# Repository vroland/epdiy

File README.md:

EPDiy E-Paper Driver
=======================================

EPDiy is a driver board which talks to affordable E-Paper (or E-Ink) screens, which are usually sold as replacement screens for E-Book readers. Why are they interesting?

* Easy on the eyes and paper-like aesthetics
* No power consumption when not updating
* Sunlight-readable

Ready-made DIY modules for this size and with 4bpp (16 Grayscale) color support are currently quite expensive and / or slow.
The EPDiy controller can drive the bare display modules, e.g. from old e-Readers, which are available for 20$ (small) / 30$ (large) on ebay!
Additionally, since it is based on the ESP32S3 (V7) / ESP32 (V2-V6) microcontroller, it features WiFi and Bluetooth connectivity.

The EPDiy driver board targets a range of E-Paper displays, as shown in the table below.
As the driving method for all matrix-based E-ink displays is more or less the same, only the right connector and timings are needed.
The current V7 board has three different display connectors, other display will require an adapter board.

The controller is optimized for the use with LiPo batteries, featuring a LiPo charger and ultra-low deep sleep current.

This project supports a driver for the ESP-IDF and Arduino. For installation instructions, please refer to the [documentation](https://epdiy.readthedocs.io/en/latest/getting_started.html#getting-your-board).
Note that for epdiy V7, update speeds are significantly lower when using the Arduino IDE, because it does not allow to change
the sub-optimal cache configuration.

Get Inspired
------------

The `examples` directory contains some example applications like a weather station or a screen diagnostic test. 
If you want to build something more useful though, how about:

- A serial terminal for connecting to a raspberry pi: [video](https://cdn.hackaday.io/files/1681937195969312/terminal_demo.mp4) [repository](https://github.com/vroland/epdiy-terminal)]
- A Music Player Daemon (MPD) dashboard: [repository](https://github.com/vroland/epdiy-mpd)]
- Firmware for displaying images directly from Immich (Self-Hosted Photo Management) [epdiy-immich](https://github.com/vroland/epdiy-immich)
- An e-Paper picture frame: [video](https://www.youtube.com/watch?v=r7AcNQsSZUw)
- And more to come!

Building It
-----------

On the [EPDiy Hardware Page](https://vroland.github.io/epdiy-hardware/), you'll find a list of all boards and variants, adapters, and helpers.
Next to each board, there are manufacturing files (gerbers), Bill of Materials (BoM), part placement files,
and 3D models ready to use!

For ordering from JLCPCB for example, ordering is as easy as downloading the zipped gerbers, BoM, and placement file
and uploading them. The process is very similar for other manufacturers, check your vendor's documentation for details.
Don't forget to oder adapters if the board doesn't have connectors for your specific display.

The current latest version is epdiy V7, beased on the ESP32S3. 
Older versions are also available on the hardware page.

#### Contributing Hardware

Want to contribute your own board variant or adapter? 
Check out the [epdiy-hardware repository](https://github.com/vroland/epdiy-hardware) for instructions.

Gettings Started
----------------

For instructions and more information visit the [documentation](https://epdiy.readthedocs.io/en/latest/getting_started.html)!

Join the Discussion
----------------

 -  Matrix Community: +epdiy:matrix.vroland.de
 - Slack: See badge

Displays
--------

|Name      |Size |Resolution|Compatible|Connector|Pin count|Compatible since pcb version|Notes
| --:      | --: | --:       | --:         | --:                  | --: | --: | --: |
| ED060SC4 | 6"  | 800 x 600<br>167 PPI | yes, tested | FH26W-39S-0.3SHW(60) | 39  | v2  |     |
|ED097OC4|9.7"|1200 x 825<br>150 PPI|yes, tested|XF2M-3315-1A|33|v2|Cheap, inferior contrast
|ED097TC2|9.7"|1200 x 825<br>150 PPI|yes, tested|XF2M-3315-1A|33|v2|Slightly higher price, better contrast
|ED097OC1|9.7"|1200 x 825<br>150 PPI|yes (should work)|XF2M-3315-1A|33|v2|Cheap, inferior performance
|ED047TC1|4.7"|960 x 540<br>234 PPI|yes, tested|40-pin|40|LILYGO 4.7" EPD|Supported only by 4.7" e-paper board by LILYGO
| ED050SC5 | 5" | 600 x 800<br>200 PPI | yes, tested       | THD0510-33CL-GF | 33 | v5 |
| ED050SC3 | 5" | 600 x 800<br>200 PPI | yes (should work) | THD0510-33CL-GF | 33 | v5 |
| ED052TC4 | 5.2" | 1280 x 780<br>??? PPI | yes (should work) | WP27D-P050VA3 | 50 | v5 |
| ED133UT2 | 13.3" | 1600 x 1200<br>150 PPI | yes, tested | adapter board | 39 | v2 | Adapter Board required, also PENG133D
| ED060XC3 | 6" | 758 x 1024<br>212 PPI | yes, tested | THD0515-34CL-SN | 34 | v5 | Cheapest, good contrast and resolution
| ED060XD4 | 6"  | 758 x 1024<br>212 PPI | yes, tested | THD0515-34CL-SN | 34 | v5 |
| ED060XC5 | 6"  | 758 x 1024<br>212 PPI | yes (should work as ED060XC3) | THD0515-34CL-SN | 34 | v5 |
| ED060XD6 | 6"  | 758 x 1024<br>212 PPI | yes (should work as ED060XC3) | THD0515-34CL-SN | 34 | v5 |
| ED060XH2 | 6"  | 758 x 1024<br>212 PPI | yes (should work as ED060XC3) | THD0515-34CL-SN | 34 | v5 |
| ED060XC9 | 6"  | 758 x 1024<br>212 PPI | yes (should work as ED060XC3) | THD0515-34CL-SN | 34 | v5 |
| ED060KD1 | 6"  | 1072 x 1448<br>300 PPI | yes (should work as ED060XC3) | THD0515-34CL-SN | 34 | v5 |
| ED060KC1 | 6"  | 1072 x 1448<br>300 PPI | yes (should work as ED060XC3) | THD0515-34CL-SN | 34 | v5 |
| ED060SCF | 6" | 600 x 800<br>167 PPI | yes, tested | THD0515-34CL-SN | 34 | v5 | Different flex cable shape
| ED060SCN | 6" | 600 x 800<br>167 PPI | yes (should work as ED060XC3) | THD0515-34CL-SN | 34 | v5 | Different flex cable shape
| ED060SCP | 6" | 600 x 800<br>167 PPI | yes (should work as ED060XC3) | THD0515-34CL-SN | 34 | v5 | Different flex cable shape
| ED060SC7 | 6" | 600 x 800<br>167 PPI | yes (should work) | AXT334124 | 34 | v5 | connector dropped in v6
| ED060SCG | 6"  | 600 x 800<br>167 PPI | yes (should work) | AXT334124 | 34 | v5 | connector dropped in v6
| ED060SCE | 6"  | 600 x 800<br>167 PPI | yes (should work) | AXT334124 | 34 | v5 | connector dropped in v6
| ED060SCM | 6"  | 600 x 800<br>167 PPI | yes (should work) | AXT334124 | 34 | v5 | connector dropped in v6
| ED060SCT | 6"  | 600 x 800<br>167 PPI | yes, tested       | AXT334124 | 34 | v5 | connector dropped in v6
| ED078KC1 | 7.8"  | 1872 x 1404<br>300 PPI | yes, tested     | FH12-40S-0.5SH | 40 | v7 | 16 data lines

Troubleshooting
---------------

The following list is compiled from past experiences and GitHub issues:
 * **The displayed image displays only part of the image.** Make sure to select the correct display type as described [here](https://epdiy.readthedocs.io/en/latest/getting_started.html#selecting-a-display-type).
 * **The existing image fades / darkens when updating a partial screen region.** Make sure the VCOM voltage is [calibrated](https://epdiy.readthedocs.io/en/latest/getting_started.html#calibrate-vcom) for your specific display.
 * **The second third of the image is replaced with the last third.** This seems to be a timing issue we could not yet quite figure out the reason for. For a workarround or suggestions please [join the discussion](https://github.com/vroland/epdiy/issues/15).
 * **The ESP does not boot correctly when external periperals are connected.** Make sure not to pull GPIO12 high during boot, as it is a strapping pin internal voltage selection (https://github.com/vroland/epdiy/issues/17).
 * **The ESP power consumption in deep sleep is too high.** Add `rtc_gpio_isolate(GPIO_NUM_12);` to your solution. See also [Configuring IOs (Deep-sleep Only)](https://docs.espressif.com/projects/esp-idf/en/latest/esp32/api-reference/system/sleep_modes.html?highlight=rtc_gpio_isolate#configuring-ios-deep-sleep-only).

LilyGo Boards
---------------

### Supported LilyGo Boards

| Board | Display | Board Definition | Notes |
| --: | --: | --: | --: |
| LilyGo T5 4.7" | ED047TC1 | `epd_board_lilygo_t5_47` | Original T5 4.7" |
| LilyGo T5 S3 E-Paper Pro | ED047TC1 | `epd_board_v7` | ESP32-S3 based, includes GT911 touch, PCF8563 RTC, BQ25896/BQ27220 battery management |

### Power Management

There are several differences with these boards.
One particular one is the way the LilyGo handles power to the display the official lilygo code has two states.
This is now handled in epdiy in a different way to the lilygo code.
**epd_poweroff()** completely turns the power off to the display and the other peripherals of the lilygo.
The new function **epd_powerdown()** keeps the peripherals on (this allows the touch functions to continue to work).
**epd_poweroff() should always be called before sleeping the system**
You can still use touch to wake the screen with the following.
In Arduino it works like this.
`epd_poweroff();`

 `epd_deinit();`

 `esp_sleep_enable_ext1_wakeup(GPIO_SEL_13, ESP_EXT1_WAKEUP_ANY_HIGH);`

 `esp_deep_sleep_start();`

### I2C Bus Sharing

EPDIY now uses the ESP-IDF master bus/device I2C driver on IDF 5.x and newer.

Existing programs can keep calling `epd_init(...)` and EPDIY will create and own the board's default I2C bus.

If your application already owns an ESP-IDF I2C master bus, pass it in during initialization:

```c
i2c_master_bus_handle_t bus = ...;
EpdI2cConfig i2c_config = {
    .bus_handle = bus,
};
EpdInitConfig init_config = {
    .i2c = &i2c_config,
};

epd_init_with_config(&epd_board_v7, &ED047TC1, EPD_LUT_64K, &init_config);
```

When a bus handle is provided, EPDIY will attach its TPS65185/PCA9555 devices to that bus and leave bus ownership to the caller.

More on E-Paper Displays
------------------------

 * List of E-Paper devices and their screens: https://e-ink-reader.ru/chg_dsp_en.php (thanks, @mcer12)
 * Reverse engineering of display pins, possible starting point for alternative drivers: https://linux-sunxi.org/PocketBook_Touch_Lux_3 (thanks, @mcer12)
 * Reverse engineering and explanation on driving EPDs: http://essentialscrap.com/eink/index.html
 * Earlier take on driving 6" EPDs with an ESP32, basis of original power circuit: http://spritesmods.com/?art=einkdisplay&page=1
 * Related Hackaday projects: https://hackaday.io/project/21607 https://hackaday.io/project/11537

If you know any other useful resources or have suggestions, please comment on #31!

Hackaday Project
----------------

For more details, see the project page on Hackaday: https://hackaday.io/project/168193-epdiy-976-e-paper-controller

Licenses
--------

The weather example is Copyright (c) David Bird 2018 (except for minor modifications). Please refer to `examples/weather/README.md` for details.

The board and schematic are licensed under a  <a rel="license" href="https://creativecommons.org/licenses/by-sa/4.0/">Creative Commons Attribution-ShareAlike 4.0 International License</a>.

Firmware and remaining examples are licensed under the terms of the GNU Lesser GPL version 3.
Utilities are licensed under the terms of the MIT license.

### Checked V7 power transitions

Applications that need to recover from a display supply failure can use
`epd_poweron_checked()` and `epd_poweroff_checked()` on board V7. Draw only after
power-on returns `ESP_OK`, and check shutdown too. Other boards return
`ESP_ERR_NOT_SUPPORTED` without changing power; the existing void power API is
still available for legacy callers.

V7 waits up to 500 ms **per power-good phase**, using the monotonic microsecond
clock. Polls yield for 10 ms (at least one FreeRTOS tick). PCA9555 and TPS65185
transfers have a 50 ms timeout, including writes and cleanup. A phase can overrun
its deadline by one bounded transfer or poll; setup and shutdown take additional
time. These constants live in `src/board/power_timing.h`.

On a failed start, V7 attempts both shutdown writes and returns the original
error. A cleanup failure is logged separately: if I2C is broken, software cannot
guarantee physical rail shutdown. The checked VCOM preparation callback follows
the same rules. Legacy void callers cannot inspect the returned status and
should migrate before relying on automatic recovery.

Run `python3 test/host/test_power.py` for host fault tests at two tick rates.

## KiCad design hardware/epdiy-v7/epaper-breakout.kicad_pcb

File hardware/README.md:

KiCad project of the breakout board.

<br />This work is licensed under a <a rel="license" href="http://creativecommons.org/licenses/by/4.0/">Creative Commons Attribution 4.0 International License</a>.

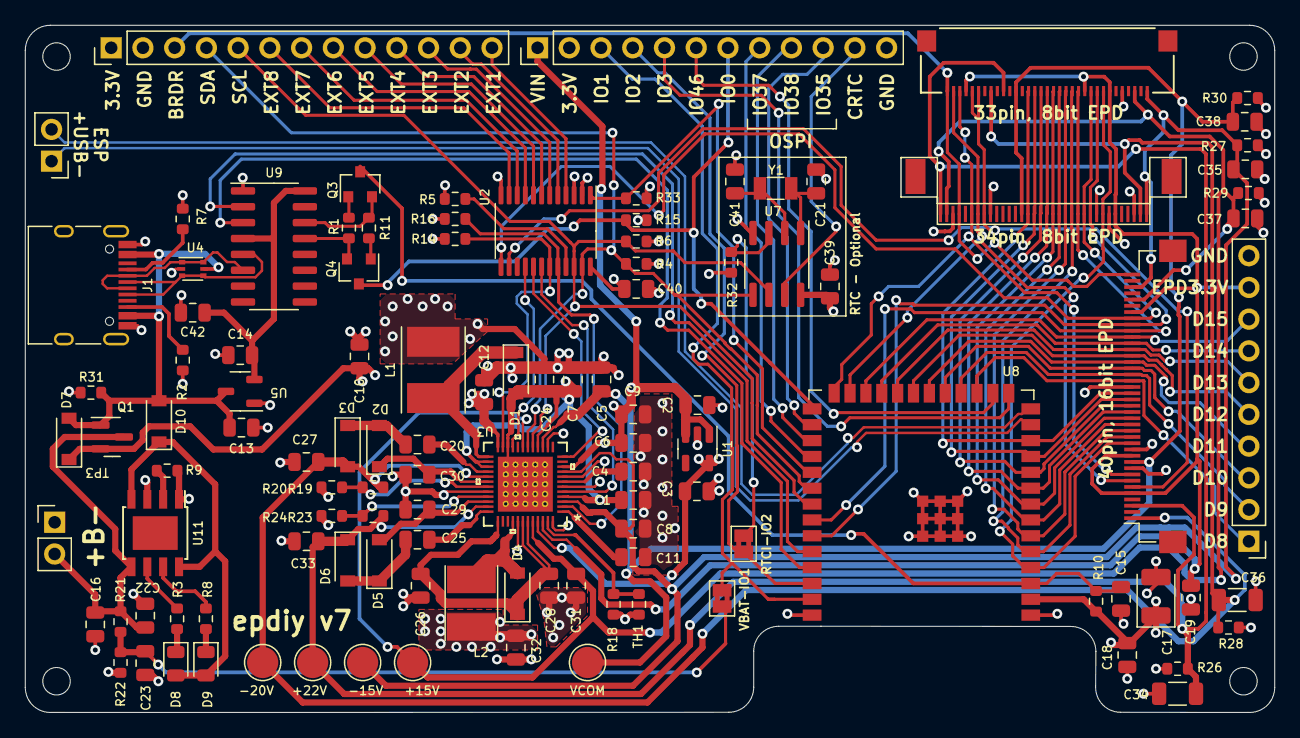
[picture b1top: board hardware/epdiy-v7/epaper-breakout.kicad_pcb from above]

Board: 4 copper layers, 100.0 x 55.0 mm, 117 parts (0 on the bottom side), 100 nets.

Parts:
C1, C4, C5, C7, C8, C11, C24, C26, C28, C31: 4.7uF; C_0805_2012Metric
C2, C3, C9, C12, C16, C19, C32: 10uF; C_0805_2012Metric
C6, C10: 22uF; C_0805_2012Metric
C13, C14, C18: 1uF; C_0805_2012Metric
C15, C22, C23, C29, C30, C39, C40, C42: 100nF; C_0805_2012Metric
C17: 100uF; CP_EIA-3528-15_AVX-H
C20, C25: 10nF; C_0805_2012Metric
C21, C41: 12pF; C_0805_2012Metric
C27, C33: 2.2uF; C_0805_2012Metric
C34, C36: 1uF/50V; C_1206_3216Metric
C35, C37, C38: 1uF/25V; C_0805_2012Metric
D1, D2, D3, D4, D5, D6, D7: MBR0540; D_SOD-123
D8: LED GREEN; LED_0805_2012Metric
D9: LED RED; LED_0805_2012Metric
D10: 1N5817; D_SOD-123
H1, H2, H3, H4: MountingHole; MountingHole_2.2mm_M2
J1: USB_C_Receptacle_USB2.0; USB_C_Receptacle_HRO_TYPE-C-31-M-12
J2: EXTENSION_HEADER; PinHeader_1x13_P2.54mm_Vertical
J3: USB_HDR; PinHeader_1x02_P2.54mm_Vertical
J4: XF2M-3315-1A; CONN_ED097OC4
J5: CONN_BAT; PinHeader_1x02_P2.54mm_Vertical
J6: 8BIT_HEADER; PinHeader_1x10_P2.54mm_Vertical
J7: ESP_HDR; PinHeader_1x12_P2.54mm_Vertical
JP1: VBAT_GPIO2; SolderJumper-2_P1.3mm_Bridged2Bar_Pad1.0x1.5mm
JP2: RTCINT_GPIO1; SolderJumper-2_P1.3mm_Bridged2Bar_Pad1.0x1.5mm
L1: 4.7uH; L_Taiyo-Yuden_NR-50xx_HandSoldering
L2: 2.2uH; L_Taiyo-Yuden_NR-40xx_HandSoldering
Q1: AO3401A; SOT-23
Q3, Q4: MMBT3904; SOT-23
R1, R4, R6, R10, R11, R14, R15, R16, R32, R33: 10k; R_0603_1608Metric
R2, R7: 5.1k; R_0603_1608Metric
R3, R8: 1k; R_0603_1608Metric
R5: 0; R_0603_1608Metric
R9: 6.8k; R_0603_1608Metric
R18: 43k; R_0603_1608Metric
R19, R23: 1M; R_0603_1608Metric
R20: 52.3k; R_0603_1608Metric
R21: 680k; R_0603_1608Metric
R22: 150k; R_0603_1608Metric
R24: 47.5k; R_0603_1608Metric
R26, R27, R28, R29: 47k; R_0603_1608Metric
R30, R31: 100k; R_0603_1608Metric
TH1: 10k/3380K; R_0603_1608Metric
TP1: +22V; TestPoint_Pad_D2.5mm
TP2: -15V; TestPoint_Pad_D2.5mm
TP3: -20V; TestPoint_Pad_D2.5mm
TP4: +15V; TestPoint_Pad_D2.5mm
TP5: VCOM; TestPoint_Pad_D2.5mm
U1: RT9080-33GJ5; TSOT-23-5
U2: PCA9535PW; TSSOP-24_4.4x7.8mm_P0.65mm
U3: TPS651851RSLR
U4: USBLC6-2P6; SOT-666
U5: XC6206PxxxMR; SOT-23-3
U6: ED078KH6; Hirose_FH12-40S-0.5SH_1x40-1MP_P0.50mm_Horizontal
U7: PCF8563T; SOIC-8_3.9x4.9mm_P1.27mm
U8: ESP32-S3-WROOM-1
U9: CH340C; SOIC-16_3.9x9.9mm_P1.27mm
U10: ED060XC5; X05A20H34G
U11: TP4056; TP4056_SOP-8-PP
Y1: 32.768K; Crystal_SMD_3215-2Pin_3.2x1.5mm

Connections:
3.3V: C3.2, C17.1, C18.2, C39.2, C40.1, J2.1, J7.2, R4.1, R6.1, R10.2, R14.1, R15.2, R16.1, R32.2, R33.1, U1.5 (VOUT), U2.24 (VDD), U3.45 (VIN3P3), U7.8 (VDD), U8.2 (3V3)
/15V: C31.2, C37.1, J4.3 (VPOS), R29.1, TP4.1, U3.19 (VPOS_DIS), U3.44 (VPOS), U6.36 (VPOS), U10.33 (VPOS)
/+22V: C33.1, C34.1, D6.1 (K), J4.24 (VGG), R23.1, R26.1, TP1.1, U3.35 (VDDH_DIS), U6.3 (VGH), U10.34 (VGG)
/-15V: C8.2, C35.1, J4.1 (VNEG), R27.1, TP2.1, U3.3 (VNEG), U3.9 (VNEG_DIS), U6.38 (VNEG), U10.1 (VNEG)
/-20V: C27.2, C36.1, D3.2 (A), J4.26 (VEE), R19.1, R28.1, TP3.1, U3.29 (VEE_DIS), U6.1 (VGL), U10.2 (VEE)
/BORDER: J2.3, J4.33 (BORDER), U6.40 (BORDER), U10.31 (BORDER)
/CKV: J4.32 (CKV), U6.7 (CKV), U8.25 (GPIO48/SPICLK_N/SUBSPICLK_N_DIFF), U10.28 (CKV)
/D0: J4.13 (D0), U6.14 (D0), U8.5 (GPIO5/TOUCH5/ADC1_CH4), U10.13 (D0)
/D1: J4.14 (D1), U6.15 (D1), U8.6 (GPIO6/TOUCH6/ADC1_CH5), U10.14 (D1)
/D2: J4.15 (D2), U6.16 (D2), U8.7 (GPIO7/TOUCH7/ADC1_CH6), U10.15 (D2)
/D3: J4.16 (D3), U6.17 (D3), U8.8 (GPIO15/U0RTS/ADC2_CH4/XTAL_32K_P), U10.16 (D3)
/D4: J4.17 (D4), U6.18 (D4), U8.9 (GPIO16/U0CTS/ADC2_CH5/XTAL_32K_NH5), U10.17 (D4)
/D5: J4.18 (D5), U6.19 (D5), U8.10 (GPIO17/U1TXD/ADC2_CH6), U10.18 (D5)
/D6: J4.19 (D6), U6.20 (D6), U8.11 (GPIO18/U1RXD/ADC2_CH7/CLK_OUT3), U10.19 (D6)
/D7: J4.20 (D7), U6.21 (D7), U8.12 (GPIO8/TOUCH8/ADC1_CH7/SUBSPICS1), U10.20 (D7)
/D8: J6.1, U6.23 (D8), U8.17 (GPIO9/TOUCH9/ADC1_CH8/FSPIHD/SUBSPIHD)
/D9: J6.2, U6.24 (D9), U8.18 (GPIO10/TOUCH10/ADC1_CH9/FSPICS0/FSPIIO4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)
/D10: J6.3, U6.25 (D10), U8.19 (GPIO11/TOUCH11/ADC2_CH0/FSPID/FSPIIO5/S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)
/D11: J6.4, U6.26 (D11), U8.20 (GPIO12/TOUCH12/ADC2_CH1/FSPICLK/FSPIIO6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)
/D12: J6.5, U6.27 (D12), U8.21 (GPIO13/TOUCH13/ADC2_CH2/FSPIQ/FSPIIO7/S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)
/D13: J6.6, U6.28 (D13), U8.22 (GPIO14/TOUCH14/ADC2_CH3/FSPIWP/FSPIDQS/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)
/D14: J6.7, U6.29 (D14), U8.23 (GPIO21)
/D15: J6.8, U6.30 (D15), U8.24 (GPIO47/SPICLK_P/SUBSPICLK_P_DIFF)
/EN: C15.1, Q3.3 (C), R10.1, U8.3 (EN)
/EP_MODE: J4.28 (MODE2), J4.29 (MODE1), U2.14 (IO1_1), U6.6 (Mode), U10.27 (MODE1)
/EP_OE: J4.10 (OEH), U2.13 (IO1_0), U6.33 (XOE), U10.11 (XOE)
/EP_STV: J4.31 (STV), U6.8 (SPV), U8.26 (GPIO45), U10.29 (SPV)
/EP_VCOM: C5.2, C38.1, J4.22 (VCOM), R30.1, TP5.1, U3.15 (VCOM), U6.10 (VCOM), U10.21 (VCOM)
/ESP_USB+: J3.2, U8.14 (GPIO20/U1CTS/ADC2_CH9/CLK_OUT1/USB_D+)
/ESP_USB-: J3.1, U8.13 (GPIO19/U1RTS/ADC2_CH8/CLK_OUT2/USB_D-)
/EXT1: J2.13, U2.4 (IO0_0)
/EXT2: J2.12, U2.5 (IO0_1)
/EXT3: J2.11, U2.6 (IO0_2)
/EXT4: J2.10, U2.7 (IO0_3)
/EXT5: J2.9, U2.8 (IO0_4)
/EXT6: J2.8, U2.9 (IO0_5)
/EXT7: J2.7, U2.10 (IO0_6)
/EXT8: J2.6, U2.11 (IO0_7)
/GPIO_1: J7.3, JP1.1 (A), U8.39 (GPIO1/TOUCH1/ADC1_CH0)
/GPIO_2: J7.4, JP2.2 (B), U8.38 (GPIO2/TOUCH2/ADC1_CH1)
/GPIO_3: J7.5, U8.15 (GPIO3/TOUCH3/ADC1_CH2)
/GPIO_35: J7.10, U8.28 (SPIIO6/GPIO35/FSPID/SUBSPID)
/GPIO_36: J7.9, U8.29 (SPIIO7/GPIO36/FSPICLK/SUBSPICLK)
/GPIO_37: J7.8, U8.30 (SPIDQS/GPIO37/FSPIQ/SUBSPIQ)
/GPIO_46: J7.6, U8.16 (GPIO46)
/IO0: J7.7, Q4.3 (C), R15.1, U8.27 (GPIO0/BOOT)
/LEH: J4.9 (LEH), U6.32 (XLE), U8.35 (MTMS/GPIO42), U10.10 (XLE)
/RTC_CLK: J7.11, U7.7 (CLKO)
/RTC_INT: JP2.1 (A), R32.1, U7.3 (~INT)
/SCL: J2.5, R6.2, U2.22 (SCL), U3.17 (SCL), U7.6 (SCL), U8.33 (MTDO/GPIO40/CLK_OUT2)
/SDA: J2.4, R4.2, U2.23 (SDA), U3.18 (SDA), U7.5 (SDA), U8.32 (MTCK/GPIO39/CLK_OUT3/SUBSPICS1)
/TPS_PWRUP: U2.16 (IO1_3), U3.21 (PWRUP)
/TPS_PWR_GOOD: R14.2, U2.19 (IO1_6), U3.23 (PWR_GOOD)
/TPS_VCOM_CTRL: U2.17 (IO1_4), U3.12 (VCOM_CTRL)
/TPS_WAKEUP: U2.18 (IO1_5), U3.5 (WAKEUP)
/TPS_nINT: R16.2, U2.20 (IO1_7), U3.2 (NINT)
/UART_3.3V: C14.2, C42.2, U5.2 (VO), U9.4 (V3), U9.16 (VCC)
/USB_D+: J1.A6 (D+), J1.B6 (D+), U4.3 (I/O2), U4.4 (I/O2), U9.5 (UD+)
/USB_D-: J1.A7 (D-), J1.B7 (D-), U4.1 (I/O1), U4.6 (I/O1), U9.6 (UD-)
/USB_RXD: U8.37 (U0TXD/GPIO43/CLK_OUT1), U9.3 (RXD)
/USB_TXD: U8.36 (U0RXD/GPIO44/CLK_OUT2), U9.2 (TXD)
/VNEG_IN: C1.1, C7.1, C24.1, D1.2 (A), U3.4 (VNEG_IN), U3.16 (VCOM_PWR), U3.22 (PBKG), U3.26 (VN), U3.27 (VEE_IN), U3.49 (EPAD)
/XCL: J4.8 (CKH), U6.13 (XCL), U8.4 (GPIO4/TOUCH4/ADC1_CH3), U10.8 (XCL)
/XSTL: J4.12 (STH), U6.31 (XSTL), U8.34 (MTDI/GPIO41/CLK_OUT1), U10.12 (XSTL)
/~DTR: Q4.2 (E), R1.2, U9.13 (~DTR)
/~GPIO_INTR: R33.2, U2.1 (~INT), U8.31 (GPIO38/FSPIWP/SUBSPIWP)
/~RTS: Q3.2 (E), R11.2, U9.14 (~RTS)
BAT+: C16.2, C22.2, J5.2, Q1.3 (D), R21.1, U11.5 (BAT)
EPD_VDD: C19.1, J4.7 (VDD), J4.11 (RL), J4.30 (UD), J6.9, U3.46 (V3P3), U6.5 (VDD), U6.11 (VDD), U6.34 (TEST), U10.6 (VDD)
GND: C1.2, C2.2, C3.1, C4.1, C5.1, C6.1, C7.2, C8.1, C9.2, C10.1, C11.1, C12.2, C13.1, C14.1, C15.2, C16.1, C17.2, C18.1, C19.2, C21.1, C22.1, C23.1, C24.2, C26.1, C27.1, C28.1, C29.1, C30.2, C31.1, C32.1, C33.2, C34.2, C35.2, C36.2, C37.2, C38.2, C39.1, C40.2, C41.1, C42.1, J1.A1 (GND), J1.A12 (GND), J1.B1 (GND), J1.B12 (GND), J1.S1 (SHIELD), J2.2, J4.5 (VSS), J5.1, J6.10, J7.12, L1.2, R2.2, R5.2, R7.2, R9.1, R18.1, R20.2, R22.2, R24.2, R26.2, R27.2, R28.2, R29.2, R30.2, R31.2, TH1.2, U1.2 (GND), U2.2 (A1), U2.3 (A2), U2.12 (VSS), U3.6 (DGND), U3.8 (AGND1), U3.14 (VCOM_DIS), U3.32 (PGND2), U3.41 (PGND1), U3.48 (AGND2), U4.2 (GND), U5.1 (GND), U6.9 (VSS), U6.12 (VSS), U6.22 (VSS), U7.4 (VSS), U8.1 (GND), U8.40 (GND), U8.41 (GND), U9.1 (GND), U10.3 (VSS), U10.7 (VSS), U10.9 (VSS), U10.26 (VSS), U10.32 (VSS), U11.1 (TEMP), U11.3 (GND)
unnamed: D1.1 (K), L1.1, U3.25 (VN_SW)
unnamed: C20.1, D2.2 (A), D3.1 (K)
unnamed: C30.1, D2.1 (K), U3.30 (VEE_D)
unnamed: D4.2 (A), L2.2, U3.40 (VB_SW)
unnamed: C26.2, C28.2, D4.1 (K), U3.37 (VDDH_IN), U3.42 (VB), U3.43 (VPOS_IN)
unnamed: C29.2, D5.2 (A), U3.34 (VDDH_D)
unnamed: C25.1, D5.1 (K), D6.2 (A)
unnamed: D8.1 (K), R3.2
unnamed: D9.1 (K), R8.2
unnamed: D8.2 (A), D9.2 (A), D10.1 (K), U11.4 (VCC), U11.8 (CE)
unnamed: J1.A5 (CC1), R7.1
unnamed: J1.B5 (CC2), R2.1
unnamed: C23.2, JP1.2 (B), R21.2, R22.1
unnamed: Q3.1 (B), R1.1
unnamed: Q4.1 (B), R11.1
unnamed: R5.1, U2.21 (A0)
unnamed: C4.2, U3.7 (INT_LDO)
unnamed: R18.2, TH1.1, U3.47 (TS)
unnamed: C25.2, U3.36 (VDDH_DRV)
unnamed: R23.2, R24.1, U3.33 (VDDH_FB)
unnamed: C20.2, U3.28 (VEE_DRV)
unnamed: R19.2, R20.1, U3.31 (VEE_FB)
unnamed: C11.2, U3.1 (VREF)
unnamed: C21.2, U7.1 (OSCI), Y1.1
unnamed: C41.2, U7.2 (OSCO), Y1.2
unnamed: R9.2, U11.2 (PROG)
unnamed: R8.1, U11.7 (~CHRG)
unnamed: R3.1, U11.6 (~STDBY)
VBUS: C13.2, D7.2 (A), D10.2 (A), J1.A4 (VBUS), J1.A9 (VBUS), J1.B4 (VBUS), J1.B9 (VBUS), Q1.1 (G), R31.1, U4.5 (VBUS), U5.3 (VI)
VIN: C2.1, C6.2, C9.1, C10.2, C12.1, C32.2, D7.1 (K), J7.1, L2.1, Q1.2 (S), U1.1 (VIN), U1.3 (EN), U3.10 (VIN), U3.24 (VIN_P)

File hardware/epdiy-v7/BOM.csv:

Comment,Designator,Footprint,LCSC
"22uF","C6,C10","Capacitor_SMD:C_0805_2012Metric","C45783"
"4.7uF","C1,C4,C5,C7,C8,C11,C24,C26,C28,C31","Capacitor_SMD:C_0805_2012Metric","C1779"
"100nF","C15,C16,C21,C22,C23,C29,C30,C39,C40","Capacitor_SMD:C_0805_2012Metric","C49678"
"100uF","C17","Capacitor_Tantalum_SMD:CP_EIA-3528-15_AVX-H"," C16133"
"1uF","C13,C14,C18","Capacitor_SMD:C_0805_2012Metric","C28323"
"10uF","C2,C3,C9,C12,C19,C32","Capacitor_SMD:C_0805_2012Metric","C15850"
"10nF","C20,C25","Capacitor_SMD:C_0805_2012Metric","C1710"
"2.2uF","C27,C33","Capacitor_SMD:C_0805_2012Metric","C49217"
"1uF/50V","C34,C36","Capacitor_SMD:C_1206_3216Metric","C1848"
"1uF/25V","C35,C37,C38","Capacitor_SMD:C_0805_2012Metric","C28323"
"1N5817","D7,D10","Diode_SMD:D_SOD-123"," C8598"
"MBR0540","D1,D2,D3,D4,D5,D6","Diode_SMD:D_SOD-123","C21353"
"LED GREEN","D8","LED_SMD:LED_0805_2012Metric","C2297"
"LED RED","D9","LED_SMD:LED_0805_2012Metric"," C84256"
"MountingHole","H1,H2,H3","MountingHole:MountingHole_2.2mm_M2",""
"XF2M-3315-1A","J1","epaper-breakout:CONN_ED097OC4","C231420"
"C10418","J2","epaper-breakout:USB_Micro-B_A01SB141B1-067","C10418"
"Conn_02x05_Counter_Clockwise","J3","Connector_PinHeader_2.54mm:PinHeader_2x05_P2.54mm_Vertical",""
"ED060SC4","J4","epaper-breakout:HRS_FH26W-39S-0.3SHW(60)","C519255"
"Conn_01x02_Female","J5","Connector_PinHeader_2.54mm:PinHeader_1x02_P2.54mm_Vertical",""
"Conn_01x12","J7","Connector_PinHeader_2.54mm:PinHeader_2x06_P2.54mm_Vertical",""
"Jumper","JP_BAT1","Jumper:SolderJumper-2_P1.3mm_Bridged2Bar_RoundedPad1.0x1.5mm",""
"4.7uH","L1","Inductor_SMD:L_Taiyo-Yuden_NR-50xx_HandSoldering"," C222947"
"2.2uH","L2","Inductor_SMD:L_Taiyo-Yuden_NR-40xx_HandSoldering","C92959"
"MMBT3904","Q3,Q4","Package_TO_SOT_SMD:SOT-23","C20526"
"10k","R1,R4,R6,R10,R11,R13,R14,R15,R16,R25","Resistor_SMD:R_0603_1608Metric","C25804"
"43k","R18","Resistor_SMD:R_0603_1608Metric","C23172"
"400","R2","Resistor_SMD:R_0603_1608Metric","C23151"
"52.3k","R20","Resistor_SMD:R_0603_1608Metric","C23196"
"680k","R21","Resistor_SMD:R_0603_1608Metric","C25822"
"150k","R22","Resistor_SMD:R_0603_1608Metric","C22807"
"1M","R19,R23","Resistor_SMD:R_0603_1608Metric","C22935"
"47.5k","R24","Resistor_SMD:R_0603_1608Metric","C25819"
"47k","R26,R27,R28,R29","Resistor_SMD:R_0603_1608Metric","C25819"
"100k","R7,R30","Resistor_SMD:R_0603_1608Metric","C25803"
"0","R5","Resistor_SMD:R_0603_1608Metric",""
"1k","R3,R8","Resistor_SMD:R_0603_1608Metric","C21190"
"6.8k","R9","Resistor_SMD:R_0603_1608Metric","C23212"
"10k/3380K","TH1","Resistor_SMD:R_0603_1608Metric","C76589"
"+22V","TP1","TestPoint:TestPoint_Pad_D2.5mm",""
"-15V","TP2","TestPoint:TestPoint_Pad_D2.5mm",""
"-20V","TP3","TestPoint:TestPoint_Pad_D2.5mm",""
"+15V","TP4","TestPoint:TestPoint_Pad_D2.5mm",""
"VCOM","TP5","TestPoint:TestPoint_Pad_D2.5mm",""
"MCP1700-3302E_SOT23","U1","Package_TO_SOT_SMD:SOT-23","C39051"
"TP4056","U11","epaper-breakout:TP4056_SOP-8-PP"," C16581"
"CH340C","U12","Package_SO:SOIC-16_3.9x9.9mm_P1.27mm"," C84681"
"PCA9535PW","U2","Package_SO:TSSOP-24_4.4x7.8mm_P0.65mm","C255606"
"TPS651851RSLR","U3","tps65185:TPS651851RSLR","C139292"
"XC6206PxxxMR","U4","Package_TO_SOT_SMD:SOT-23"," C5446"
"ESP32-WROVER","U5","esp32-wrover:ESP32-WROVER"," C503591"
"ED060XC5","U6","epaper-breakout:X05A20H34G","C528053"
"TPS2113APW","U7","epaper-breakout:TPS2113APW","C130052"

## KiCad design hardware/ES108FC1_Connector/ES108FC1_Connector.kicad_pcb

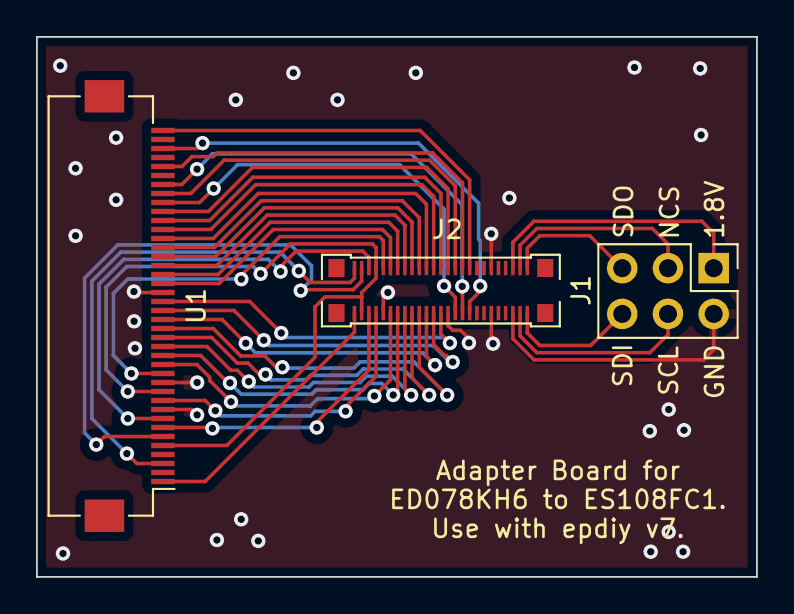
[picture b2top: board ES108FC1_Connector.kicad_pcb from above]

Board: 2 copper layers, 40.0 x 30.0 mm, 3 parts (0 on the bottom side), 37 nets.

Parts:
J1: Conn_02x03_Odd_Even; PinHeader_2x03_P2.54mm_Vertical
J2: ES108FC1
U1: ED078KH6; Hirose_FH12-40S-0.5SH_mirrored

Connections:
/BRD: J2.34 (Border), U1.40 (BORDER)
/CKV: J2.5 (CKV), U1.7 (CKV)
/D0: J2.11 (D0), U1.14 (D0)
/D1: J2.13 (D1), U1.15 (D1)
/D2: J2.15 (D2), U1.16 (D2)
/D3: J2.17 (D3), U1.17 (D3)
/D4: J2.19 (D4), U1.18 (D4)
/D5: J2.21 (D5), U1.19 (D5)
/D6: J2.23 (D6), U1.20 (D6)
/D7: J2.25 (D7), U1.21 (D7)
/D8: J2.12 (D8), U1.23 (D8)
/D9: J2.14 (D9), U1.24 (D9)
/D10: J2.16 (D10), U1.25 (D10)
/D11: J2.18 (D11), U1.26 (D11)
/D12: J2.20 (D12), U1.27 (D12)
/D13: J2.22 (D13), U1.28 (D13)
/D14: J2.24 (D14), U1.29 (D14)
/D15: J2.26 (D15), U1.30 (D15)
/MODE: J2.4 (MODE), U1.6 (Mode)
/SPI_NCS: J1.3, J2.48 (SPI_NCS)
/SPI_SCL: J1.4, J2.47 (SPI_SCL)
/SPI_SDI: J1.6, J2.49 (SPI_SDI)
/SPI_SDO: J1.5, J2.50 (SPI_SDO)
/SPI_VDD: J1.1, J2.46 (VDD2)
/SPV: J2.6 (SPV), U1.8 (SPV)
/TEST: J2.31 (XON), U1.34 (TEST)
/VCOM: J2.7 (VCOM), U1.10 (VCOM)
/VGH: J2.2 (VGH), U1.3 (VGH)
/VGL: J2.1 (VGL), U1.1 (VGL)
/VNEG: J2.33 (VNEG), U1.38 (VNEG)
/VPOS: J2.32 (VPOS), U1.36 (VPOS)
/XCL: J2.10 (XCL), U1.13 (XCL)
/XLE: J2.29 (XLE), U1.32 (XLE)
/XOE: J2.30 (XOE), U1.33 (XOE)
/XSTL: J2.28 (XSTL), U1.31 (XSTL)
GND: J1.2, J2.9 (VSS), J2.27 (VSS), J2.39 (VSS), J2.40 (VSS), J2.45 (VSS), U1.9 (VSS), U1.12 (VSS), U1.22 (VSS)
VDD: J2.3 (VDD), J2.8 (VDD), U1.5 (VDD), U1.11 (VDD)

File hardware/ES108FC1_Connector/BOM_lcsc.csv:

Comment,Designator,Footprint,LCSC
"Conn_02x03_Odd_Even","J1","Connector_PinHeader_2.54mm:PinHeader_2x03_P2.54mm_Vertical",""
"ES108FC1","J2","epaper-breakout:ES108FC1","C2880696"
"ED078KH6","U1","epaper-breakout:Hirose_FH12-40S-0.5SH_mirrored","C202114"

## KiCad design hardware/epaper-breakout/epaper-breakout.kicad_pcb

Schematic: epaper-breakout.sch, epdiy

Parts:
C1, C4, C5, C7, C8, C11, C24, C26, C28, C31: 4.7uF; C_0805_2012Metric; LCSC C1779
C2, C3, C9, C12, C32: 10uF; C_0805_2012Metric; LCSC C15850
C6, C10: 22uF; C_0805_2012Metric; LCSC C45783
C13, C14, C18: 1uF; C_0805_2012Metric; LCSC C28323
C15, C16, C21, C22, C23, C29, C30, C39, C40: 100nF; C_0805_2012Metric; LCSC C49678
C17: 100uF; CP_EIA-3528-15_AVX-H; LCSC C16133
C19: 10uF; C_0805_2012Metric; LCSC C19702
C20, C25: 10nF; C_0805_2012Metric; LCSC C1710
C27, C33: 2.2uF; C_0805_2012Metric; LCSC C49217
C34, C36: 1uF/50V; C_1206_3216Metric; LCSC C1848
C35, C37, C38: 1uF/25V; C_0805_2012Metric; LCSC C28323
D1, D2, D3, D4, D5, D6: MBR0540; D_SOD-123; LCSC C21353
D7, D10: 1N5817; D_SOD-123; LCSC C8598
D8: LED GREEN; LED_0805_2012Metric; LCSC C2297
D9: LED RED; LED_0805_2012Metric; LCSC C84256
H1, H2, H3: MountingHole; MountingHole_2.2mm_M2
J1: XF2M-3315-1A; CONN_ED097OC4; LCSC C231420
J2: C10418; USB_Micro-B_A01SB141B1-067; LCSC C10418
J3: Conn_02x05_Counter_Clockwise; PinHeader_2x05_P2.54mm_Vertical
J4: ED060SC4; HRS_FH26W-39S-0.3SHW(60); LCSC C519255
J5: Conn_01x02_Female; PinHeader_1x02_P2.54mm_Vertical
J7: Conn_01x12; PinHeader_2x06_P2.54mm_Vertical
JP_BAT1: Jumper; SolderJumper-2_P1.3mm_Bridged2Bar_RoundedPad1.0x1.5mm
L1: 4.7uH; L_Taiyo-Yuden_NR-50xx_HandSoldering; LCSC C222947
L2: 2.2uH; L_Taiyo-Yuden_NR-40xx_HandSoldering; LCSC C92959
Q3, Q4: MMBT3904; SOT-23; LCSC C20526
R1, R4, R6, R10, R11, R13, R14, R15, R16, R25: 10k; R_0603_1608Metric; LCSC C25804
R2: 400; R_0603_1608Metric; LCSC C23151
R3, R8: 1k; R_0603_1608Metric; LCSC C21190
R5: 0; R_0603_1608Metric
R7, R30: 100k; R_0603_1608Metric; LCSC C25803
R9: 6.8k; R_0603_1608Metric; LCSC C23212
R18: 43k; R_0603_1608Metric; LCSC C23172
R19, R23: 1M; R_0603_1608Metric; LCSC C22935
R20: 52.3k; R_0603_1608Metric; LCSC C23196
R21: 680k; R_0603_1608Metric; LCSC C25822
R22: 150k; R_0603_1608Metric; LCSC C22807
R24: 47.5k; R_0603_1608Metric; LCSC C25819
R26, R27, R28, R29: 47k; R_0603_1608Metric; LCSC C25819
TH1: 10k/3380K; R_0603_1608Metric; LCSC C76589
TP1: +22V; TestPoint_Pad_D2.5mm
TP2: -15V; TestPoint_Pad_D2.5mm
TP3: -20V; TestPoint_Pad_D2.5mm
TP4: +15V; TestPoint_Pad_D2.5mm
TP5: VCOM; TestPoint_Pad_D2.5mm
U1: MCP1700-3302E_SOT23; SOT-23; LCSC C39051
U2: PCA9535PW; TSSOP-24_4.4x7.8mm_P0.65mm; LCSC C255606
U3: TPS651851RSLR; LCSC C139292
U4: XC6206PxxxMR; SOT-23; LCSC C5446
U5: ESP32-WROVER; LCSC C503591
U6: ED060XC5; X05A20H34G; LCSC C528053
U7: TPS2113APW; LCSC C130052
U11: TP4056; TP4056_SOP-8-PP; LCSC C16581
U12: CH340C; SOIC-16_3.9x9.9mm_P1.27mm; LCSC C84681

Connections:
/15V: C31.2, C37.1, J1.3 (VPOS), J4.2 (VPOS), R29.1, TP4.1, U3.19 (VPOS_DIS), U3.44 (VPOS), U6.33 (VPOS)
/+3.3V: C3.2, C17.1, C18.2, C40.1, J3.6, J7.1, R4.1, R6.1, R10.1, R14.1, R15.1, R16.1, R25.1, U1.2 (VO), U2.24 (VDD), U3.45 (VIN3P3), U5.2 (3V3)
/+3.3_Serial: C14.2, C16.1, U4.2 (VO), U12.4 (V3), U12.16 (VCC)
/+22V: C33.1, C34.1, D6.1 (K), J1.24 (VGG), J4.23 (GVDD), R23.1, R26.1, TP1.1, U3.35 (VDDH_DIS), U6.34 (VGG)
/-15V: C8.2, C35.1, J1.1 (VNEG), J4.1 (VNEG), R27.1, TP2.1, U3.3 (VNEG), U3.9 (VNEG_DIS), U6.1 (VNEG)
/-20V: C27.2, C36.1, D3.2 (A), J1.26 (VEE), J4.24 (GVEE), R19.1, R28.1, TP3.1, U3.29 (VEE_DIS), U6.2 (VEE)
/A0: J3.3, JP_BAT1.1, U5.6 (IO34)
/EN: C15.1, Q3.3 (C), R10.2, U5.3 (EN)
/EP_CKH: J1.8 (CKH), J4.5 (CLK), U5.23 (IO15), U6.8 (XCL)
/EP_CKV: J1.32 (CKV), J4.33 (U1CKV), J4.38 (U2CKV), U5.11 (IO26), U6.28 (CKV)
/EP_D0: J1.13 (D0), J4.12 (D0), U5.10 (IO25), U6.13 (D0)
/EP_D1: J1.14 (D1), J4.13 (D1), U5.26 (IO4), U6.14 (D1)
/EP_D2: J1.15 (D2), J4.14 (D2), U5.29 (IO5), U6.15 (D2)
/EP_D3: J1.16 (D3), J4.15 (D3), U5.30 (IO18), U6.16 (D3)
/EP_D4: J1.17 (D4), J4.16 (D4), U5.31 (IO19), U6.17 (D4)
/EP_D5: J1.18 (D5), J4.17 (D5), U5.33 (IO21), U6.18 (D5)
/EP_D6: J1.19 (D6), J4.18 (D6), U5.36 (IO22), U6.19 (D6)
/EP_D7: J1.20 (D7), J4.19 (D7), U5.37 (IO23), U6.20 (D7)
/EP_LE: J1.9 (LEH), J4.6 (LE), R13.1, U5.24 (IO2), U6.10 (XLE)
/EP_MODE: J1.28 (MODE2), J1.29 (MODE1), J4.27 (GMODE2), J4.28 (GMODE1), U2.14 (IO1_1), U6.27 (MODE1)
/EP_OE: J1.10 (OEH), J4.7 (OE), U2.13 (IO1_0), U6.11 (XOE)
/EP_STH: J1.12 (STH), J4.11 (SPH), U5.12 (IO27), U6.12 (XSTL)
/EP_STV: J1.31 (STV), J4.32 (U1SPV), J4.37 (U2SPV), U2.15 (IO1_2), U6.29 (SPV)
/EP_VCOM: C5.2, C38.1, J1.22 (VCOM), J4.22 (VCOM), R30.1, TP5.1, U3.15 (VCOM), U6.21 (VCOM)
/IO0: J3.7, Q4.3 (C), R15.2, U5.25 (IO0)
/MISO: J3.10, U5.14 (IO12)
/MOSI: J3.8, U5.16 (IO13)
/SCL: J7.4, R6.2, U2.22 (SCL), U3.17 (SCL), U5.9 (IO33_XTAL_32K_N)
/SCLK: J3.9, U5.13 (IO14)
/SDA: J7.3, R4.2, U2.23 (SDA), U3.18 (SDA), U5.8 (IO32_XTAL_32K_P)
/SENSOR_VN: J3.2, U5.5 (SENSOR_VN_IO39)
/SENSOR_VP: J3.1, U5.4 (SENSOR_VP_IO36)
/TPS_PWRUP: U2.16 (IO1_3), U3.21 (PWRUP)
/TPS_PWR_GOOD: R14.2, U2.19 (IO1_6), U3.23 (PWR_GOOD)
/TPS_VCOM_CTRL: U2.17 (IO1_4), U3.12 (VCOM_CTRL)
/TPS_WAKEUP: U2.18 (IO1_5), U3.5 (WAKEUP)
/TPS_nINT: R16.2, U2.20 (IO1_7), U3.2 (NINT)
/USB_D+: J2.3 (D+), U12.5 (UD+)
/USB_D-: J2.2 (D-), U12.6 (UD-)
/USB_RXD: U5.35 (TXD0), U12.3 (RXD)
/USB_TXD: U5.34 (RXD0), U12.2 (TXD)
/VNEG_IN: C1.1, C7.1, C24.1, D1.2 (A), U3.4 (VNEG_IN), U3.16 (VCOM_PWR), U3.22 (PBKG), U3.26 (VN), U3.27 (VEE_IN), U3.49 (EPAD)
/~DTR: Q4.2 (E), R1.2, U12.13 (~DTR)
/~GPIO_INTR: R25.2, U2.1 (~INT), U5.7 (IO35)
/~RTS: Q3.2 (E), R11.2, U12.14 (~RTS)
BAT+: C22.2, C39.2, J5.2, R21.1, U7.6 (IN2), U11.5 (BAT)
EPD_VDD: C19.1, J1.7 (VDD), J1.11 (RL), J1.30 (UD), J4.4 (VDD), J4.8 (SHR), J4.10 (CE2), J4.29 (RL), J4.30 (U1CE2), J4.35 (U2CE2), J4.36 (U2CE1), U3.46 (V3P3), U6.6 (VDD)
GND: C1.2, C2.1, C3.1, C4.1, C5.1, C6.1, C7.2, C8.1, C9.2, C10.1, C11.1, C12.2, C13.2, C14.1, C15.2, C16.2, C17.2, C18.1, C19.2, C21.2, C22.1, C23.1, C24.2, C26.1, C27.1, C28.1, C29.1, C30.2, C31.1, C32.1, C33.2, C34.2, C35.2, C36.2, C37.2, C38.2, C39.1, C40.2, J1.5 (VSS), J1.33 (BORDER), J2.5 (GND), J2.6 (Shield), J3.5, J4.3 (GND), J4.9 (CE1), J4.31 (U1CE1), J4.34 (VBORDER), J5.1, J7.2, L1.2, R2.2, R5.2, R7.2, R9.1, R13.2, R18.1, R20.2, R22.2, R24.2, R26.2, R27.2, R28.2, R29.2, R30.2, TH1.2, U1.1 (GND), U2.2 (A1), U2.3 (A2), U2.12 (VSS), U3.6 (DGND), U3.8 (AGND1), U3.14 (VCOM_DIS), U3.32 (PGND2), U3.41 (PGND1), U3.48 (AGND2), U4.1 (GND), U5.1 (GND), U5.15 (GND), U5.38 (GND), U5.39 (GND), U6.3 (VSS), U6.7 (VSS), U6.9 (VSS), U6.26 (VSS), U6.31 (BORDER), U6.32 (VSS), U7.2 (EN_N), U7.5 (GND), U11.1 (TEMP), U11.3 (GND), U12.1 (GND)
unnamed: C4.2, U3.7 (INT_LDO)
unnamed: C11.2, U3.1 (VREF)
unnamed: C13.1, D7.1 (K), U4.3 (VI)
unnamed: C20.1, D2.2 (A), D3.1 (K)
unnamed: C20.2, U3.28 (VEE_DRV)
unnamed: C23.2, JP_BAT1.2, R21.2, R22.1
unnamed: C25.1, D5.1 (K), D6.2 (A)
unnamed: C25.2, U3.36 (VDDH_DRV)
unnamed: C26.2, C28.2, D4.1 (K), U3.37 (VDDH_IN), U3.42 (VB), U3.43 (VPOS_IN)
unnamed: C29.2, D5.2 (A), U3.34 (VDDH_D)
unnamed: C30.1, D2.1 (K), U3.30 (VEE_D)
unnamed: D1.1 (K), L1.1, U3.25 (VN_SW)
unnamed: D4.2 (A), L2.2, U3.40 (VB_SW)
unnamed: D8.1 (K), R3.2
unnamed: D9.1 (K), R8.2
unnamed: D8.2 (A), D9.2 (A), D10.1 (K), U11.4 (VCC), U11.8 (CE)
unnamed: J7.5, U2.4 (IO0_0)
unnamed: J7.6, U2.5 (IO0_1)
unnamed: J7.7, U2.6 (IO0_2)
unnamed: J7.8, U2.7 (IO0_3)
unnamed: J7.9, U2.8 (IO0_4)
unnamed: J7.10, U2.9 (IO0_5)
unnamed: J7.11, U2.10 (IO0_6)
unnamed: J7.12, U2.11 (IO0_7)
unnamed: Q3.1 (B), R1.1
unnamed: Q4.1 (B), R11.1
unnamed: R2.1, U7.4 (ILIM)
unnamed: R3.1, U11.6 (~STDBY)
unnamed: R5.1, U2.21 (A0)
unnamed: R8.1, U11.7 (~CHRG)
unnamed: R9.2, U11.2 (PROG)
unnamed: R18.2, TH1.1, U3.47 (TS)
unnamed: R19.2, R20.1, U3.31 (VEE_FB)
unnamed: R23.2, R24.1, U3.33 (VDDH_FB)
SW_VIN: C2.2, C6.2, C9.1, C10.2, C12.1, C32.2, J3.4, L2.1, U1.3 (VI), U3.10 (VIN), U3.24 (VIN_P), U7.7 (OUT)
VBUS: C21.1, D7.2 (A), D10.2 (A), J2.1 (VBUS), R7.1, U7.3 (VSNS), U7.8 (IN1)

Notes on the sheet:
Auto-Reset
Power 3.3V
USB -> UART
Close to EPD connector

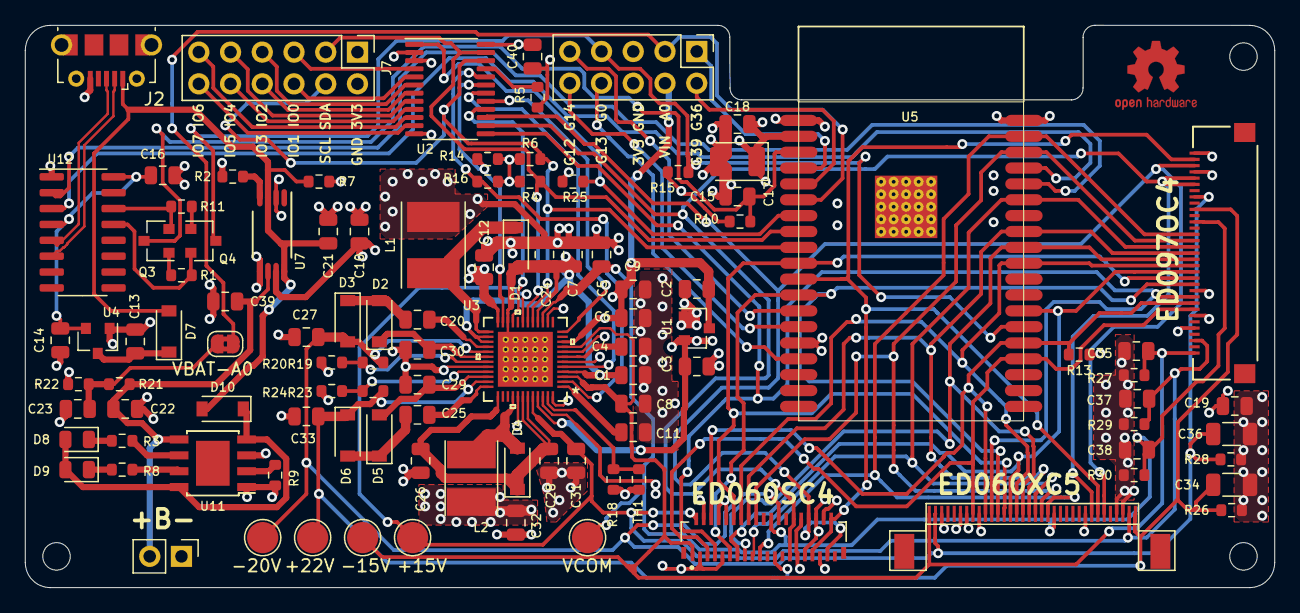
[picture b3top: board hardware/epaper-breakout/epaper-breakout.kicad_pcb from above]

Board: 4 copper layers, 100.0 x 45.0 mm, 108 parts (1 on the bottom side), 84 nets.

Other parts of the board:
CC: Symbol_CreativeCommons_SilkScreenTop_Type2_Big

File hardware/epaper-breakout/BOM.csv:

Comment,Designator,Footprint,LCSC
"22uF","C6,C10","Capacitor_SMD:C_0805_2012Metric","C45783"
"4.7uF","C1,C4,C5,C7,C8,C11,C24,C26,C28,C31","Capacitor_SMD:C_0805_2012Metric","C1779"
"0.1uF","C15,C16,C21,C22,C23,C39,C40","Capacitor_SMD:C_0805_2012Metric","C49678"
"100uF","C17","Capacitor_Tantalum_SMD:CP_EIA-3528-15_AVX-H"," C16133"
"1uF","C13,C14,C18","Capacitor_SMD:C_0805_2012Metric","C28323"
"10uF","C2,C3,C9,C12,C19,C32","Capacitor_SMD:C_0805_2012Metric","C15850"
"10nF","C20,C25","Capacitor_SMD:C_0805_2012Metric","C1710"
"100nF","C29,C30","Capacitor_SMD:C_0805_2012Metric"," C49678"
"2.2uF","C27,C33","Capacitor_SMD:C_0805_2012Metric","C49217"
"1uF/50V","C34,C36","Capacitor_SMD:C_1206_3216Metric","C1848"
"1uF/25V","C35,C37,C38","Capacitor_SMD:C_0805_2012Metric","C28323"
"1N5817","D7,D10","Diode_SMD:D_SOD-123"," C8598"
"MBR0540","D1,D2,D3,D4,D5,D6","Diode_SMD:D_SOD-123","C21353"
"LED GREEN","D8","LED_SMD:LED_0805_2012Metric","C2297"
"LED RED","D9","LED_SMD:LED_0805_2012Metric"," C84256"
"MountingHole","H1,H2,H3","MountingHole:MountingHole_2.2mm_M2",""
"XF2M-3315-1A","J1","epaper-breakout:CONN_ED097OC4","C231420"
"C10418","J2","epaper-breakout:USB_Micro-B_A01SB141B1-067","C10418"
"Conn_02x05_Counter_Clockwise","J3","Connector_PinHeader_2.54mm:PinHeader_2x05_P2.54mm_Vertical",""
"ED060SC4","J4","epaper-breakout:HRS_FH26W-39S-0.3SHW(60)","C519255"
"Conn_01x02_Female","J5","Connector_PinHeader_2.54mm:PinHeader_1x02_P2.54mm_Vertical",""
"Conn_01x12","J7","Connector_PinHeader_2.54mm:PinHeader_2x06_P2.54mm_Vertical",""
"Jumper","JP_BAT1","Jumper:SolderJumper-2_P1.3mm_Bridged2Bar_RoundedPad1.0x1.5mm",""
"4.7uH","L1","Inductor_SMD:L_Taiyo-Yuden_NR-50xx_HandSoldering"," C222947"
"2.2uH","L2","Inductor_SMD:L_Taiyo-Yuden_NR-40xx_HandSoldering","C92959"
"MMBT3904","Q3,Q4","Package_TO_SOT_SMD:SOT-23","C20526"
"10k","R1,TH1,R4,R6,R10,R11,R13,R14,R15,R16,R25","Resistor_SMD:R_0603_1608Metric","C25804"
"43k","R18","Resistor_SMD:R_0603_1608Metric","C23172"
"400","R2","Resistor_SMD:R_0603_1608Metric","C23151"
"52.3k","R20","Resistor_SMD:R_0603_1608Metric","C23196"
"680k","R21","Resistor_SMD:R_0603_1608Metric","C25822"
"150k","R22","Resistor_SMD:R_0603_1608Metric","C22807"
"1M","R19,R23","Resistor_SMD:R_0603_1608Metric","C22935"
"47.5k","R24","Resistor_SMD:R_0603_1608Metric","C25819"
"47k","R26,R27,R28,R29","Resistor_SMD:R_0603_1608Metric","C25819"
"100k","R7,R30","Resistor_SMD:R_0603_1608Metric","C25803"
"0","R5","Resistor_SMD:R_0603_1608Metric",""
"1k","R3,R8","Resistor_SMD:R_0603_1608Metric","C21190"
"6.8k","R9","Resistor_SMD:R_0603_1608Metric","C23212"
"+22V","TP1","TestPoint:TestPoint_Pad_D2.5mm",""
"-15V","TP2","TestPoint:TestPoint_Pad_D2.5mm",""
"-20V","TP3","TestPoint:TestPoint_Pad_D2.5mm",""
"+15V","TP4","TestPoint:TestPoint_Pad_D2.5mm",""
"VCOM","TP5","TestPoint:TestPoint_Pad_D2.5mm",""
"MCP1700-3302E_SOT23","U1","Package_TO_SOT_SMD:SOT-23","C39051"
"TP4056","U11","epaper-breakout:TP4056_SOP-8-PP"," C16581"
"CH340C","U12","Package_SO:SOIC-16_3.9x9.9mm_P1.27mm"," C84681"
"PCA9535PW","U2","Package_SO:TSSOP-24_4.4x7.8mm_P0.65mm","C255606"
"TPS651851RSLR","U3","tps65185:TPS651851RSLR","C139292"
"XC6206PxxxMR","U4","Package_TO_SOT_SMD:SOT-23"," C5446"
"ESP32-WROVER","U5","esp32-wrover:ESP32-WROVER"," C503591"
"ED060XC5","U6","epaper-breakout:X05A20H34G","C528053"
"TPS2113APW","U7","epaper-breakout:TPS2113APW","C130052"

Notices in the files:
hardware/epaper-breakout/epaper-breakout.sch:
License: CC-BY-SA-4.0
parts and their libraries:
Copyright 2016 Accelerated Designs. All rights reserved.
